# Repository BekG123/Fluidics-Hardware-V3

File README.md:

# Fluidics Controller PCB (V3)

A KiCad hardware design for the fluidics controller used on Cephla/Squid
microscopy systems. It drives the pumps, valves, and sensors that move and
monitor liquid through the instrument, all coordinated by an on-board
Teensy 4.1 microcontroller.

## What it does

The board is the single point of electrical control for the instrument's
liquid path. The Teensy firmware talks to each subsystem over the bus noted
below and exposes a serial interface to the host software.

## Subsystems

| Subsystem | Qty | Interface | Notes |
|---|---|---|---|
| Syringe pump | 1 | RS-232 (`J3`, DB15) | Primary fluid actuation |
| Solenoid valves | up to 7 | GPIO → `U1` TPL7407 → `J5` screw terminal | Low-side driver + per-channel status LEDs |
| Selector valves (IDEX) | 6 | Isolated I²C (5 V) | Addresses set on each valve module |
| Flow sensors | 3 | I²C @ 0x08 | One per I²C port (`J15`/`J17`/`J20`) — fixed address forces separate buses |
| Bubble sensors | 2 | Digital, level-shifted (`J2`/`J4`) | Not I²C |

Isolation and bus conditioning are handled by ADuM1250 / ISO7021 isolators,
a PCA9615 differential-I²C link, and UART/logic level shifters.

## Board specs

- **MCU:** Teensy 4.1 (footprint `U2`, on-board)
- **Stack-up:** 4-layer — `F.Cu` / `In1.Cu` (GND) / `In2.Cu` (+24 V & +5 V planes) / `B.Cu`
- **Power:** +24 V input; Pololu DC-DC regulators for +5 V; on-board LDO (`U3`) for +3.3 V
- **Mounting:** 4 corner plated holes (`H1`–`H4`), chassis GND

## Fabrication

The ready-to-order package lives in `fabrication/v3/`

## Attribution

Derived from `Fluidics-Hardware-V2` by Kevin Marx. V3 modifications by
Bekhruz Malikov (<bekhruz.malikov@cephla.com>). Built with KiCad 10.

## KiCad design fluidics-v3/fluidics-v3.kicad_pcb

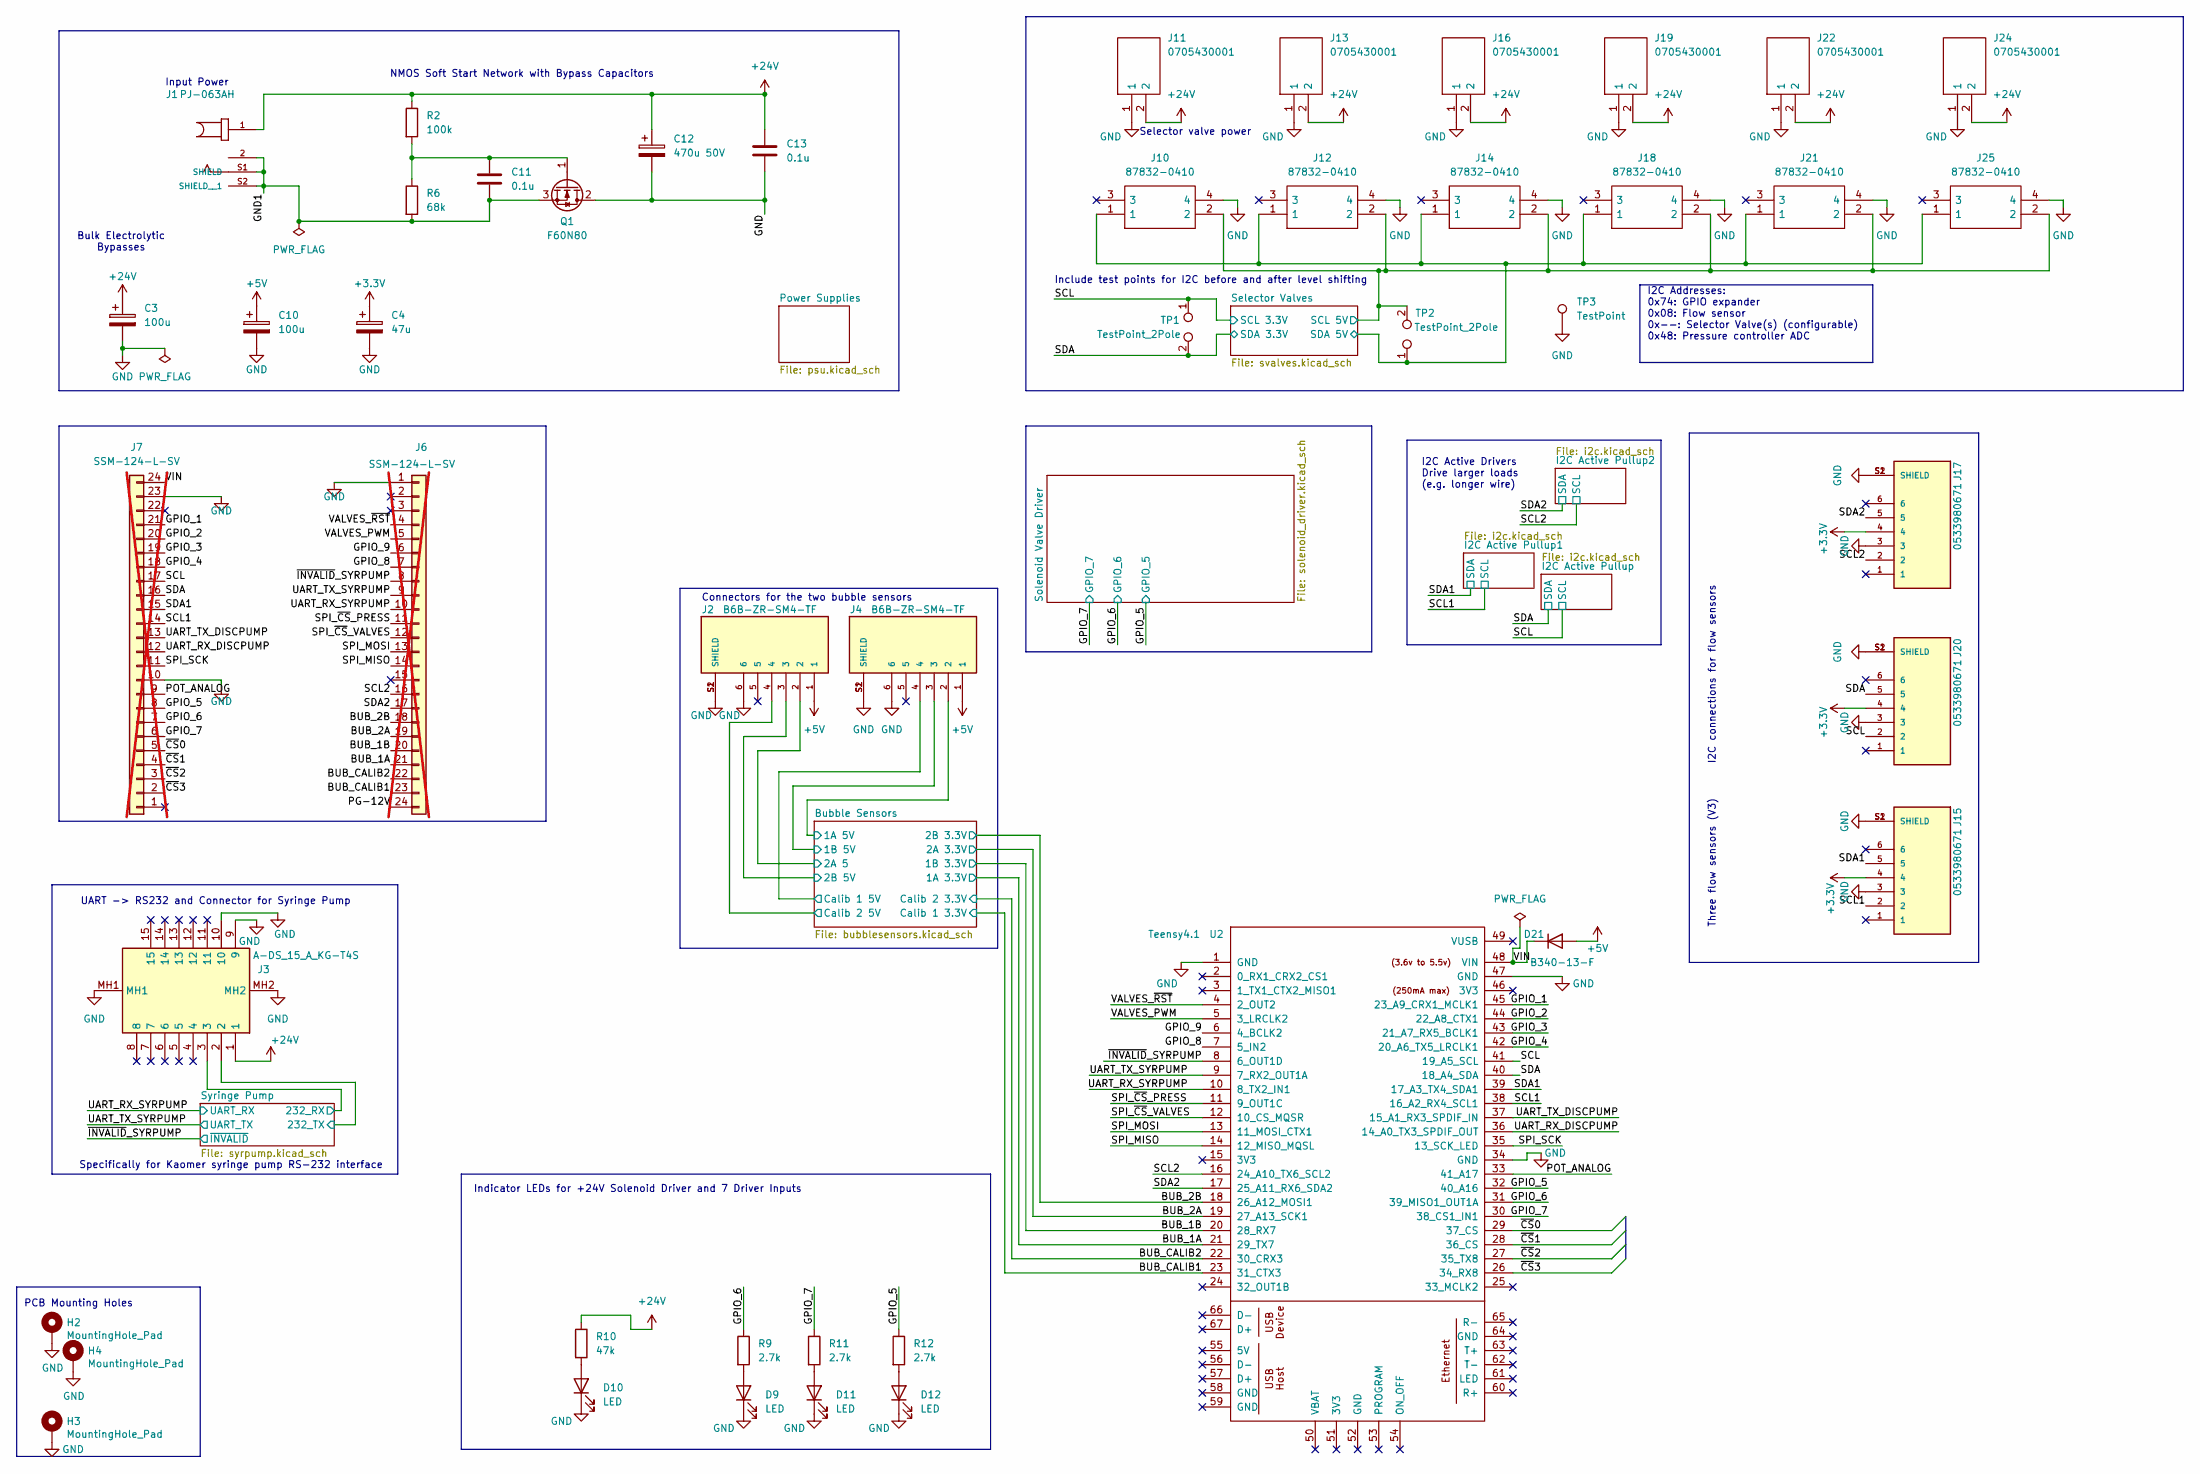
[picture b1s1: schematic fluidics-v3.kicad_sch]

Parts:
C3: 100u; CP_EIA-7343-20_Kemet-V
C4: 47u; C_1206_3216Metric
C10: 100u; C_1210_3225Metric
C11, C13: 0.1u; C_0603_1608Metric
C12: 470u 50V; CP_Radial_D10.0mm_P5.00mm
D9, D10, D11, D12: LED; LED_0402_1005Metric
D21: B340-13-F; D_SMC
H2, H3, H4: MountingHole_Pad; MountingHole_3.2mm_M3_Pad_Via
J1: PJ-063AH; CUI_PJ-063AH; Manufacturer_Part_Number PJ-063AH; LCSC C2928097
J2, J4: B6B-ZR-SM4-TF; CONN_B6B-ZR-SM4-TF_JST
J3: A-DS_15_A_KG-T4S; ADS15AKGT4S; Manufacturer_Part_Number A-DS 15 A/KG-T4S; LCSC C3100941
J6, J7: SSM-124-L-SV; PinSocket_1x24_P2.54mm_Vertical_SMD_DualLand; not fitted
J10, J12, J14, J18, J21, J25: 87832-0410; 878320410; Manufacturer_Part_Number 87832-0410; Mouser Part Number 538-87832-1010
J11, J13, J16, J19, J22, J24: 0705430001; SHDR2W64P0X254_1X2_737X660X1181P; Manufacturer_Part_Number 0705430001; Mouser Part Number N/A
J15, J17, J20: 0533980671; MOLEX_0533980671; PARTREV A
Q1: F60N80; TO-220-3_Vertical
R2: 100k; R_0402_1005Metric
R6: 68k; R_0402_1005Metric
R9, R11, R12: 2.7k; R_0402_1005Metric
R10: 47k; R_0603_1608Metric
TP1, TP2: TestPoint_2Pole; TestPoint_2Pads_Pitch2.54mm_Drill0.8mm
TP3: TestPoint; TestPoint_THTPad_1.5x1.5mm_Drill0.7mm
U2: Teensy4.1; Teensy 4.1

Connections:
+3.3V: C4.1, J15.4, J17.4, J20.4; also elsewhere on the board
+5V: C10.1, D21.2 (A), J2.1, J4.1; also elsewhere on the board
+24V: C3.1, C12.1, C13.1, J1.1, J3.1, J11.2, J13.2, J16.2, J19.2, J22.2, J24.2, R2.1, R10.1; also elsewhere on the board
/BUB_1A: J6.21, U2.21 (29_TX7); also elsewhere on the board
/BUB_1B: J6.20, U2.20 (28_RX7); also elsewhere on the board
/BUB_2A: J6.19, U2.19 (27_A13_SCK1); also elsewhere on the board
/BUB_2B: J6.18, U2.18 (26_A12_MOSI1); also elsewhere on the board
/BUB_CALIB1: J6.23, U2.23 (31_CTX3); also elsewhere on the board
/BUB_CALIB2: J6.22, U2.22 (30_CRX3); also elsewhere on the board
/Bubble Sensors/1A 5V: J4.2; also elsewhere on the board
/Bubble Sensors/1B 5V: J4.3; also elsewhere on the board
/Bubble Sensors/2A 5: J2.2; also elsewhere on the board
/Bubble Sensors/2B 5V: J2.3; also elsewhere on the board
/Bubble Sensors/Calib 1 5V: J4.4; also elsewhere on the board
/Bubble Sensors/Calib 2 5V: J2.4; also elsewhere on the board
/GND1: C11.2, J1.2, J1.S1 (SHIELD), J1.S2 (SHIELD__1), Q1.3 (S), R6.2
/GPIO_1: J7.21, U2.45 (23_A9_CRX1_MCLK1)
/GPIO_2: J7.20, U2.44 (22_A8_CTX1)
/GPIO_3: J7.19, U2.43 (21_A7_RX5_BCLK1)
/GPIO_4: J7.18, U2.42 (20_A6_TX5_LRCLK1)
/GPIO_5: J7.8, R12.1, U2.32 (40_A16); also elsewhere on the board
/GPIO_6: J7.7, R9.1, U2.31 (39_MISO1_OUT1A); also elsewhere on the board
/GPIO_7: J7.6, R11.1, U2.30 (38_CS1_IN1); also elsewhere on the board
/GPIO_8: J6.7, U2.7 (5_IN2)
/GPIO_9: J6.6, U2.6 (4_BCLK2)
/PG-12V: J6.24
/POT_ANALOG: J7.9, U2.33 (41_A17)
/SCL: J7.17, J20.2, TP1.1, U2.41 (19_A5_SCL); also elsewhere on the board
/SCL1: J7.14, J15.2, U2.38 (16_A2_RX4_SCL1); also elsewhere on the board
/SCL2: J6.16, J17.2, U2.16 (24_A10_TX6_SCL2); also elsewhere on the board
/SDA: J7.16, J20.5, TP1.2, U2.40 (18_A4_SDA); also elsewhere on the board
/SDA1: J7.15, J15.5, U2.39 (17_A3_TX4_SDA1); also elsewhere on the board
/SDA2: J6.17, J17.5, U2.17 (25_A11_RX6_SDA2); also elsewhere on the board
/SPI_MISO: J6.14, U2.14 (12_MISO_MQSL)
/SPI_MOSI: J6.13, U2.13 (11_MOSI_CTX1)
/SPI_SCK: J7.11, U2.35 (13_SCK_LED)
/SPI_~CS_PRESS: J6.11, U2.11 (9_OUT1C)
/SPI_~CS_VALVES: J6.12, U2.12 (10_CS_MQSR)
/Selector Valves/SCL 5V: J10.2, J12.2, J14.2, J18.2, J21.2, J25.2, TP2.2; also elsewhere on the board
/Selector Valves/SDA 5V: J10.1, J12.1, J14.1, J18.1, J21.1, J25.1, TP2.1; also elsewhere on the board
/Syringe Pump/232_RX: J3.3; also elsewhere on the board
/Syringe Pump/232_TX: J3.2; also elsewhere on the board
/UART_RX_DISCPUMP: J7.12, U2.36 (14_A0_TX3_SPDIF_OUT)
/UART_RX_SYRPUMP: J6.10, U2.10 (8_TX2_IN1); also elsewhere on the board
/UART_TX_DISCPUMP: J7.13, U2.37 (15_A1_RX3_SPDIF_IN)
/UART_TX_SYRPUMP: J6.9, U2.9 (7_RX2_OUT1A); also elsewhere on the board
/VALVES_PWM: J6.5, U2.5 (3_LRCLK2)
/VALVES_~RST: J6.4, U2.4 (2_OUT2)
/VIN: D21.1 (K), J7.24, U2.48 (VIN)
/~CS0: J7.5, U2.29 (37_CS)
/~CS1: J7.4, U2.28 (36_CS)
/~CS2: J7.3, U2.27 (35_TX8)
/~CS3: J7.2, U2.26 (34_RX8)
/~INVALID_SYRPUMP: J6.8, U2.8 (6_OUT1D); also elsewhere on the board
GND: C3.2, C4.2, C10.2, C12.2, C13.2, D9.1 (K), D10.1 (K), D11.1 (K), D12.1 (K), H2.1 (1_1), H3.1 (1_1), H4.1 (1_1), J2.6, J2.S1 (SHIELD), J2.S2 (SHIELD), J3.9, J3.10, J3.MH1, J3.MH2, J4.6, J4.S1 (SHIELD), J4.S2 (SHIELD), J6.1, J7.10, J7.23, J10.4, J11.1, J12.4, J13.1, J14.4, J15.3, J15.S1 (SHIELD), J15.S2 (SHIELD), J16.1, J17.3, J17.S1 (SHIELD), J17.S2 (SHIELD), J18.4, J19.1, J20.3, J20.S1 (SHIELD), J20.S2 (SHIELD), J21.4, J22.1, J24.1, J25.4, Q1.2 (D), TP3.1 (1_1), U2.1 (GND), U2.34 (GND), U2.47 (GND); also elsewhere on the board
unnamed: D9.2 (A), R9.2
unnamed: D10.2 (A), R10.2
unnamed: D11.2 (A), R11.2
unnamed: D12.2 (A), R12.2
unnamed: C11.1, Q1.1 (G), R2.2, R6.1

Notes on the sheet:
I2C connections for flow sensors
NMOS Soft Start Network with Bypass Capacitors
Indicator LEDs for +24V Solenoid Driver and 7 Driver Inputs
Bulk Electrolytic Bypasses
Three flow sensors (V3)
Include test points for I2C before and after level shifting
UART -> RS232 and Connector for Syringe Pump
PCB Mounting Holes
Input Power
Selector valve power
I2C Addresses: 0x74: GPIO expander 0x08: Flow sensor 0x--: Selector Valve(s) (configurable) 0x48: Pressure controller ADC
Specifically for Kaomer syringe pump RS-232 interface
Connectors for the two bubble sensors
I2C Active Drivers Drive larger loads (e.g. longer wire)

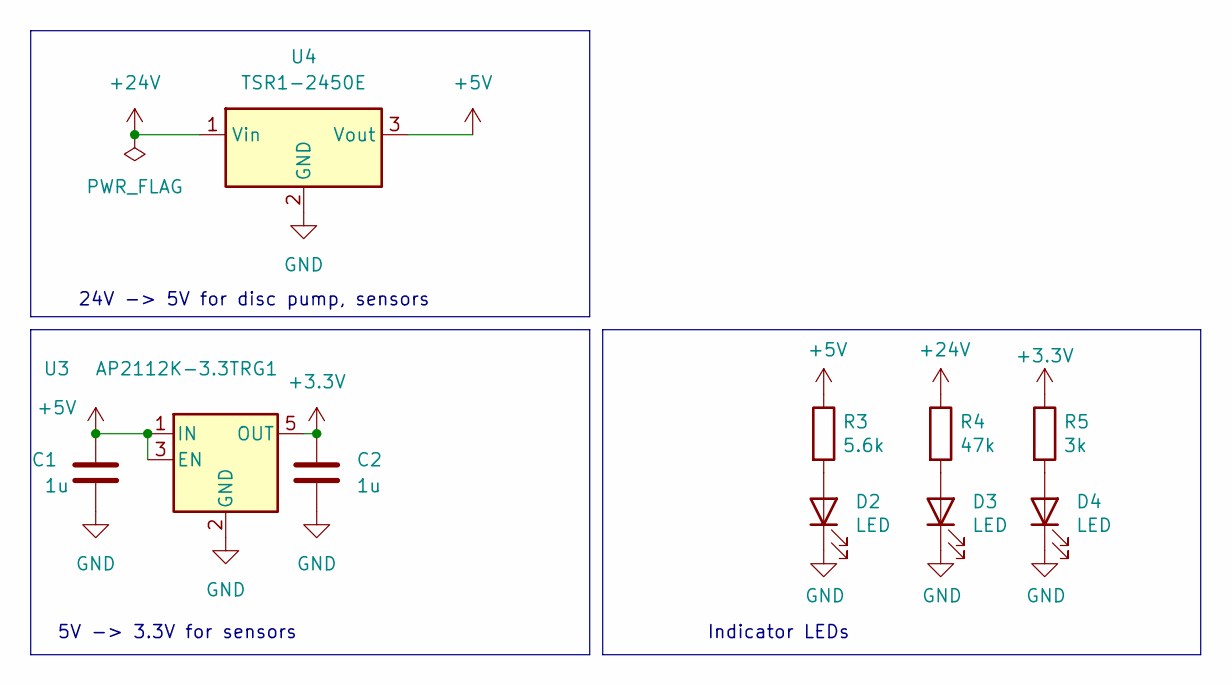
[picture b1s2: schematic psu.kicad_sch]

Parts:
C1, C2: 1u; C_0603_1608Metric
D2, D3: LED; LED_0805_2012Metric; Manufacturer_Part_Number LTST-C170TGKT; LCSC Part # C73546
D4: LED; LED_0805_2012Metric; Manufacturer_Part_Number EAST2012WA1; LCSC Part # C83960
R3: 5.6k; R_0805_2012Metric; Manufacturer_Part_Number RC0805FR-075K6L
R4: 47k; R_0402_1005Metric; Manufacturer_Part_Number RC0402FR-0747KL
R5: 3k; R_0402_1005Metric; Manufacturer_Part_Number RC0402FR-073KL
U3: AP2112K-3.3TRG1; SOT-23-5
U4: TSR1-2450E; Converter_DCDC_TRACO_TSR1-xxxxE_THT

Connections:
+3.3V: C2.1, R5.1, U3.5 (OUT); also elsewhere on the board
+5V: C1.1, R3.1, U3.1 (IN), U3.3 (EN), U4.3 (Vout); also elsewhere on the board
+24V: R4.1, U4.1 (Vin); also elsewhere on the board
GND: C1.2, C2.2, D2.1 (K), D3.1 (K), D4.1 (K), U3.2 (GND), U4.2 (GND); also elsewhere on the board
unnamed: D2.2 (A), R3.2
unnamed: D3.2 (A), R4.2
unnamed: D4.2 (A), R5.2

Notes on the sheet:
5V -> 3.3V for sensors
24V -> 5V for disc pump, sensors
Indicator LEDs

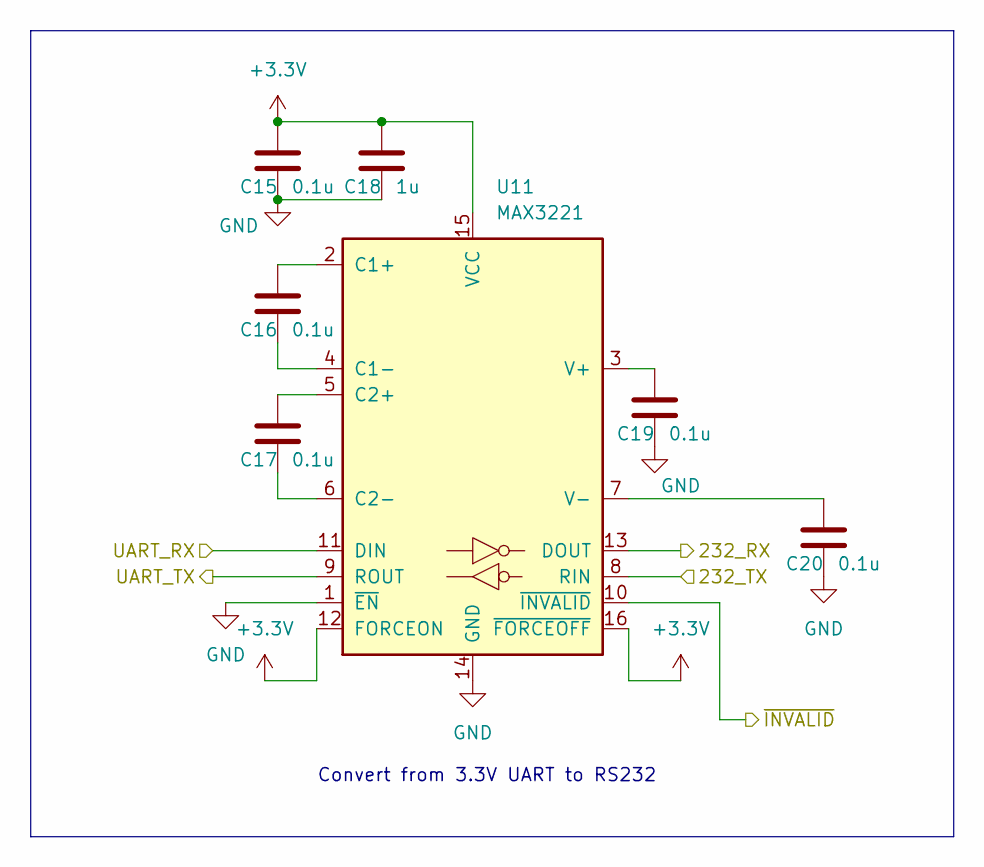
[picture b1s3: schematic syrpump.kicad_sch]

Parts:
C15, C16, C17, C19, C20: 0.1u; C_0603_1608Metric
C18: 1u; C_0805_2012Metric
U11: MAX3221; SOP65P640X120-16N

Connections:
+3.3V: C15.1, C18.1, U11.12 (FORCEON), U11.15 (VCC), U11.16 (~FORCEOFF); also elsewhere on the board
/Syringe Pump/232_RX: U11.13 (DOUT); also elsewhere on the board
/Syringe Pump/232_TX: U11.8 (RIN); also elsewhere on the board
/UART_RX_SYRPUMP: U11.11 (DIN); also elsewhere on the board
/UART_TX_SYRPUMP: U11.9 (ROUT); also elsewhere on the board
/~INVALID_SYRPUMP: U11.10 (~INVALID); also elsewhere on the board
GND: C15.2, C18.2, C19.2, C20.2, U11.1 (~EN), U11.14 (GND); also elsewhere on the board
unnamed: C16.1, U11.2 (C1+)
unnamed: C16.2, U11.4 (C1-)
unnamed: C17.1, U11.5 (C2+)
unnamed: C17.2, U11.6 (C2-)
unnamed: C19.1, U11.3 (V+)
unnamed: C20.1, U11.7 (V-)

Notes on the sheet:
Convert from 3.3V UART to RS232

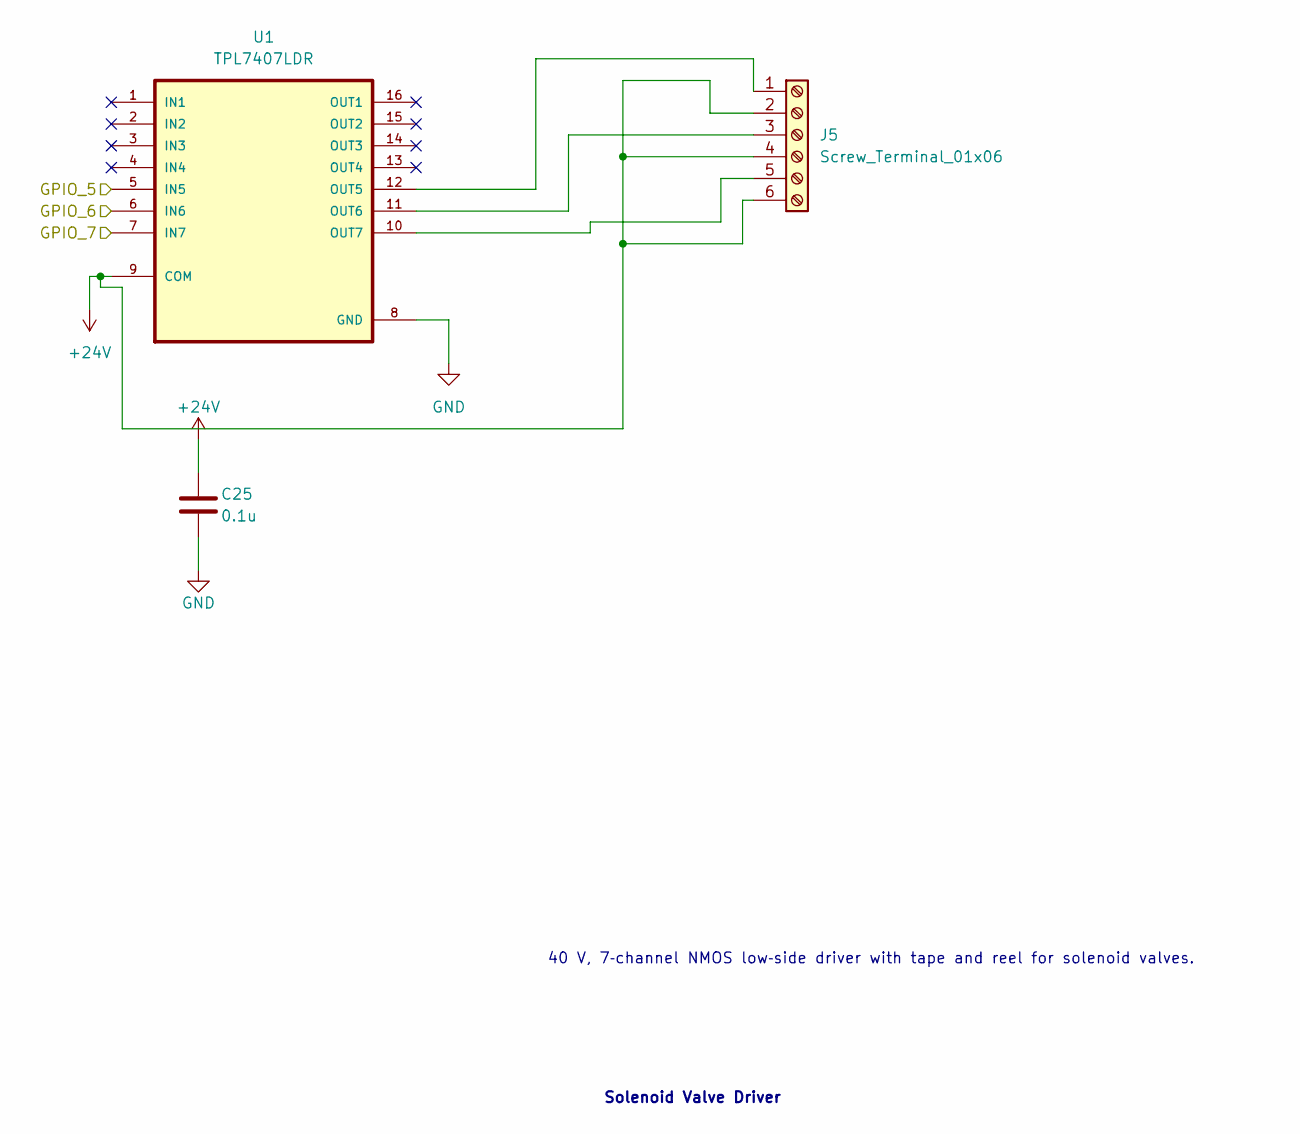
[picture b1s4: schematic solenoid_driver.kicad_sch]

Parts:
C25: 0.1u; C_0603_1608Metric
J5: Screw_Terminal_01x06; TerminalBlock_Xinya_XY308-2.54-6P_1x06_P2.54mm_Horizontal
U1: TPL7407LDR; SOIC127P600X175-16N; Manufacturer_Part_Number TPL7407LDR

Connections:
+24V: C25.1, J5.2, J5.4, J5.6, U1.9 (COM); also elsewhere on the board
/GPIO_5: U1.5 (IN5); also elsewhere on the board
/GPIO_6: U1.6 (IN6); also elsewhere on the board
/GPIO_7: U1.7 (IN7); also elsewhere on the board
GND: C25.2, U1.8 (GND); also elsewhere on the board
unnamed: J5.1, U1.12 (OUT5)
unnamed: J5.3, U1.11 (OUT6)
unnamed: J5.5, U1.10 (OUT7)

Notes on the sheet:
Solenoid Valve Driver
40 V, 7‑channel NMOS low‑side driver with tape and reel for solenoid valves.

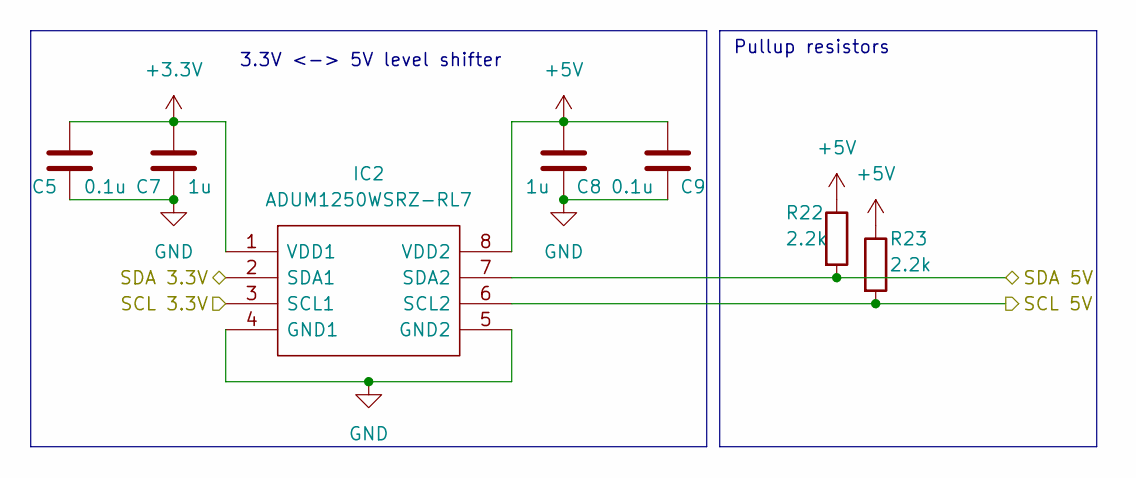
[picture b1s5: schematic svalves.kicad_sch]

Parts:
C5, C9: 0.1u; C_0603_1608Metric
C7, C8: 1u; C_0805_2012Metric
IC2: ADUM1250WSRZ-RL7; SOIC127P600X175-8N; Manufacturer_Part_Number ADUM1250WSRZ-RL7; Mouser Part Number 584-ADUM1250WSRZ-RL7
R22, R23: 2.2k; R_0402_1005Metric

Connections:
+3.3V: C5.1, C7.1, IC2.1 (VDD1); also elsewhere on the board
+5V: C8.1, C9.1, IC2.8 (VDD2), R22.1, R23.1; also elsewhere on the board
/SCL: IC2.3 (SCL1); also elsewhere on the board
/SDA: IC2.2 (SDA1); also elsewhere on the board
/Selector Valves/SCL 5V: IC2.6 (SCL2), R23.2; also elsewhere on the board
/Selector Valves/SDA 5V: IC2.7 (SDA2), R22.2; also elsewhere on the board
GND: C5.2, C7.2, C8.2, C9.2, IC2.4 (GND1), IC2.5 (GND2); also elsewhere on the board

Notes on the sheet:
Pullup resistors
3.3V <-> 5V level shifter

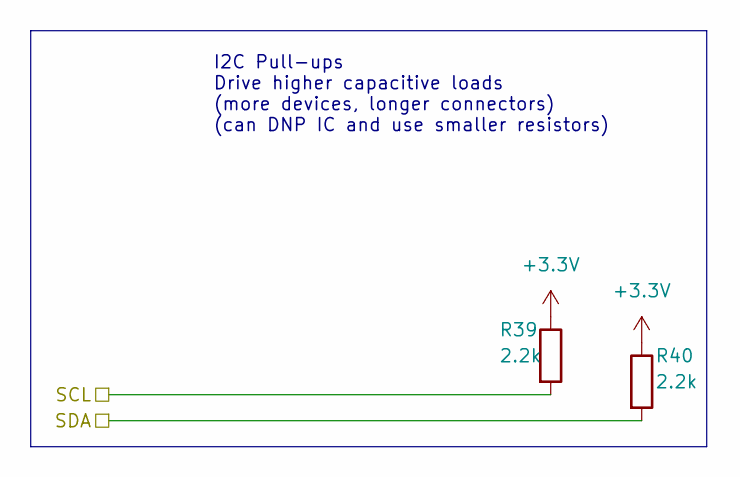
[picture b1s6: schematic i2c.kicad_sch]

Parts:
R39, R40: 2.2k; R_0402_1005Metric

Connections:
+3.3V: R39.1, R40.1; also elsewhere on the board
/SCL1: R39.2; also elsewhere on the board
/SDA1: R40.2; also elsewhere on the board

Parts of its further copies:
R41, R42, R43, R44: 2.2k; R_0402_1005Metric

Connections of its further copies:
+3.3V: R41.1, R42.1, R43.1, R44.1; also elsewhere on the board
/SCL: R43.2; also elsewhere on the board
/SCL2: R41.2; also elsewhere on the board
/SDA: R44.2; also elsewhere on the board
/SDA2: R42.2; also elsewhere on the board

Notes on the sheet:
I2C Pull-ups Drive higher capacitive loads (more devices, longer connectors) (can DNP IC and use smaller resistors)

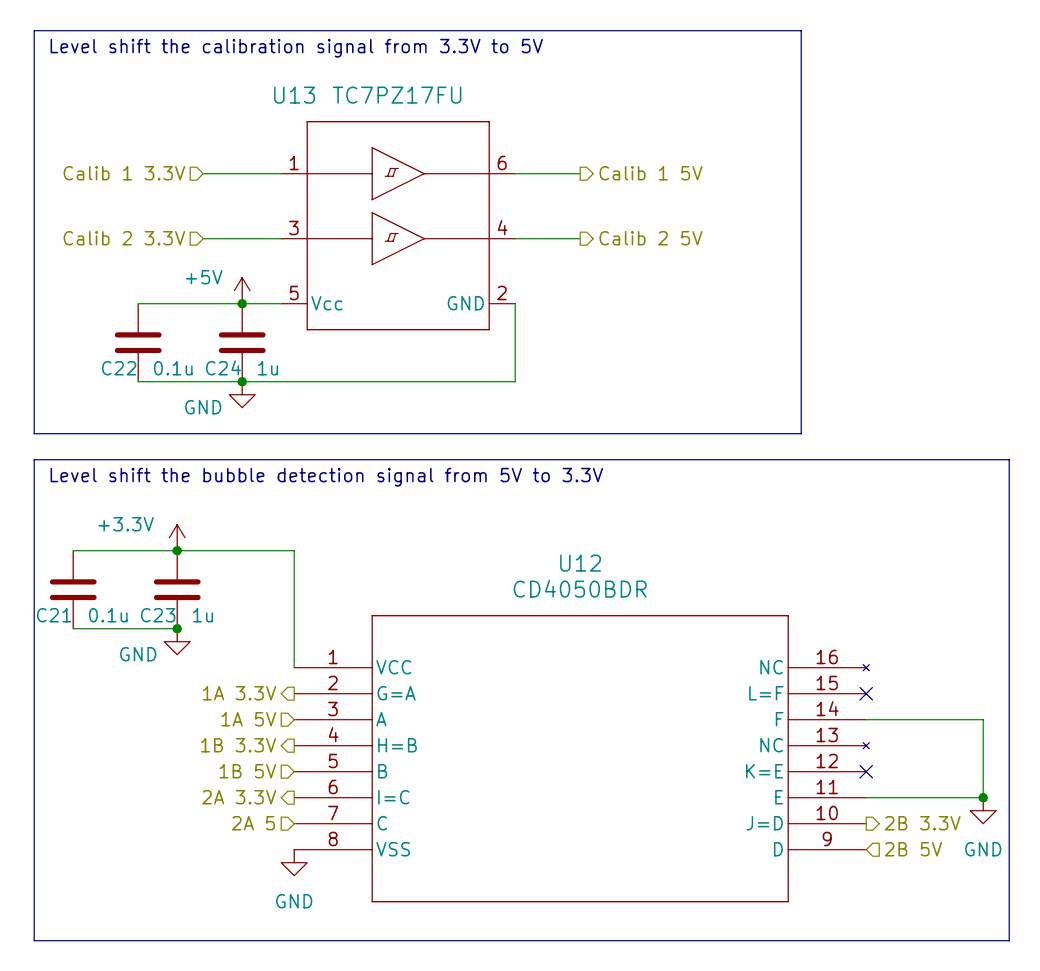
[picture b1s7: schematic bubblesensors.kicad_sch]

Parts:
C21, C22: 0.1u; C_0603_1608Metric
C23, C24: 1u; C_0805_2012Metric
U12: CD4050BDR; D16
U13: TC7PZ17FU; SOT-363 US6_TOS

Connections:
+3.3V: C21.1, C23.1, U12.1 (VCC); also elsewhere on the board
+5V: C22.1, C24.1, U13.5 (Vcc); also elsewhere on the board
/BUB_1A: U12.2 (G=A); also elsewhere on the board
/BUB_1B: U12.4 (H=B); also elsewhere on the board
/BUB_2A: U12.6 (I=C); also elsewhere on the board
/BUB_2B: U12.10 (J=D); also elsewhere on the board
/BUB_CALIB1: U13.1; also elsewhere on the board
/BUB_CALIB2: U13.3; also elsewhere on the board
/Bubble Sensors/1A 5V: U12.3 (A); also elsewhere on the board
/Bubble Sensors/1B 5V: U12.5 (B); also elsewhere on the board
/Bubble Sensors/2A 5: U12.7 (C); also elsewhere on the board
/Bubble Sensors/2B 5V: U12.9 (D); also elsewhere on the board
/Bubble Sensors/Calib 1 5V: U13.6; also elsewhere on the board
/Bubble Sensors/Calib 2 5V: U13.4; also elsewhere on the board
GND: C21.2, C22.2, C23.2, C24.2, U12.8 (VSS), U12.11 (E), U12.14 (F), U13.2 (GND); also elsewhere on the board

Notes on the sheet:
Level shift the bubble detection signal from 5V to 3.3V
Level shift the calibration signal from 3.3V to 5V

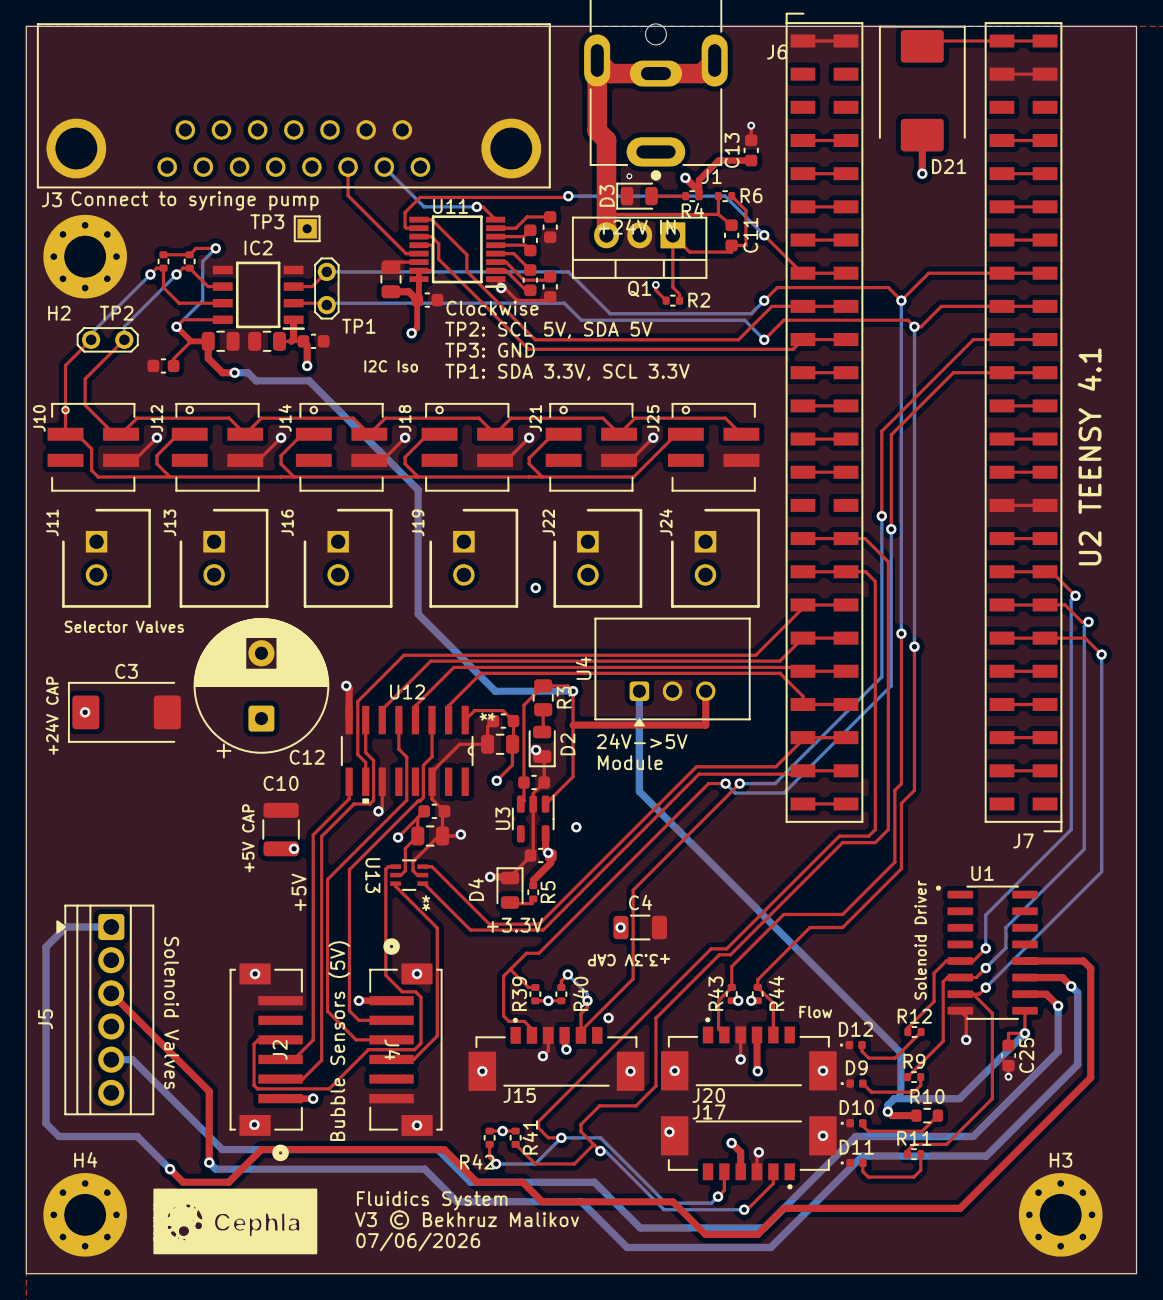
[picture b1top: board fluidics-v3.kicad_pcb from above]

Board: 4 copper layers, 85.0 x 95.5 mm, 84 parts (0 on the bottom side), 51 nets.

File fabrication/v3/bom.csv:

"Reference","Value","Footprint","QUANTITY","DNP"
"C1,C2","1u","Capacitor_SMD:C_0603_1608Metric","2",""
"C3","100u","Capacitor_Tantalum_SMD:CP_EIA-7343-20_Kemet-V","1",""
"C4","47u","Capacitor_SMD:C_1206_3216Metric","1",""
"C5,C9,C15-C17,C19-C22","0.1u","Capacitor_SMD:C_0603_1608Metric","9",""
"C6","0.01u","Capacitor_SMD:C_0603_1608Metric","1",""
"C7,C8,C18,C23,C24","1u","Capacitor_SMD:C_0805_2012Metric","5",""
"C10","100u","Capacitor_SMD:C_1210_3225Metric","1",""
"D2-D4","LED","LED_SMD:LED_0805_2012Metric","3",""
"D9-D12","LED","LED_SMD:LED_0402_1005Metric","4",""
"D21","B340-13-F","Diode_SMD:D_SMC","1",""
"H2-H4","MountingHole_Pad","MountingHole:MountingHole_3.2mm_M3_Pad_Via","3",""
"IC2","ADUM1250WSRZ-RL7","analog_devices:SOIC127P600X175-8N","1",""
"J1","PJ-063AH","barreljack:CUI_PJ-063AH","1",""
"J2,J4","B6B-ZR-SM4-TF","B6B-ZR-SM4-TF:CONN_B6B-ZR-SM4-TF_JST","2",""
"J3","A-DS_15_A_KG-T4S","db15:ADS15AKGT4S","1",""
"J5","Screw_Terminal_01x06","TerminalBlock:TerminalBlock_Xinya_XY308-2.54-6P_1x06_P2.54mm_Horizontal","1",""
"J6,J7","SSM-124-L-SV","teensy4.1:PinSocket_1x24_P2.54mm_Vertical_SMD_DualLand","2",""
"J10,J12,J14,J18,J21,J25","87832-0410","molex_connectors:878320410","6",""
"J11,J13,J16,J19,J22,J24","0705430001","molex_connectors:SHDR2W64P0X254_1X2_737X660X1181P","6",""
"J15,J17,J20","0533980671","molex_connectors:MOLEX_0533980671","3",""
"R1","0","Resistor_SMD:R_0402_1005Metric","1","DNP"
"R3","5.6k","Resistor_SMD:R_0805_2012Metric","1",""
"R4","47k","Resistor_SMD:R_0402_1005Metric","1",""
"R5","3k","Resistor_SMD:R_0402_1005Metric","1",""
"R9,R11,R12","2.7K","Resistor_SMD:R_0402_1005Metric","3",""
"R10","42K","Resistor_SMD:R_0603_1608Metric","1",""
"R22,R23,R39-R44","10k","Resistor_SMD:R_0402_1005Metric","8",""
"R51","47k","Resistor_SMD:R_0603_1608Metric_Pad0.98x0.95mm_HandSolder","1",""
"TH1","10R","Varistor:RV_Disc_D7mm_W3.9mm_P5mm","1",""
"TP1,TP2","TestPoint_2Pole","TestPoint:TestPoint_2Pads_Pitch2.54mm_Drill0.8mm","2",""
"TP3","TestPoint","TestPoint:TestPoint_THTPad_1.5x1.5mm_Drill0.7mm","1",""
"U1","TPL7407LDR","TPL7407LDR:SOIC127P600X175-16N","1",""
"U2","Teensy4.1","teensy4.1:Teensy 4.1","1",""
"U3","AP2112K-3.3TRG1","Package_TO_SOT_SMD:SOT-23-5","1",""
"U4","D24V10FX","pololu:D24V10FX","1",""
"U6","LTC4311CSC6-TRPBF","LTC:SOT-6_SC_LIT-L","1","DNP"
"U11","MAX3221","MAX232:SOP65P640X120-16N","1",""
"U12","CD4050BDR","hexbuf:D16","1",""
"U13","TC7PZ17FU","TC7PZ17FU:SOT-363   US6_TOS","1",""

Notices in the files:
fluidics-v2/fluidics-v2.kicad_pcb:
V3 © Bekhruz Malikov
